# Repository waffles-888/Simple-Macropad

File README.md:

# Simple-Macropad

The Simple Macropad is a 6 key pad with a rotary encoder and an OLED screen. It is also using QMK for its firmware.

# Features:
* 6 Keys
* OLED screen
* Rotary encoder

# CAD Model:
Everything is put together with 4 M3 screws and screws directly into the plastic. The PCB should sit snugly into the space inside the case and has a little bit of plastic extruded from the bottom to keep it flat while being used. It’s printed in two pieces, keeping it simple.

# PCB

This is the PCB which was made inside of KiCAD

# Firmware
My Hackpad uses QMK firmware for it. I want to add VIA support to allow for more customisability.

* 6 keys which will be able to change once theres VIA support
* the rotary encoder allows for volume to be changed
* The OLED screen shows HackPad

# BOM:
* 6x Cherry MX Switches
* 6x 3D printed Keycaps
* 4x M3x16mm screws
* 1x 0.91" 128x32 OLED Display
* 1x EC11 Rotary Encoder
* 1x XIAO RP2040
* 1x Case

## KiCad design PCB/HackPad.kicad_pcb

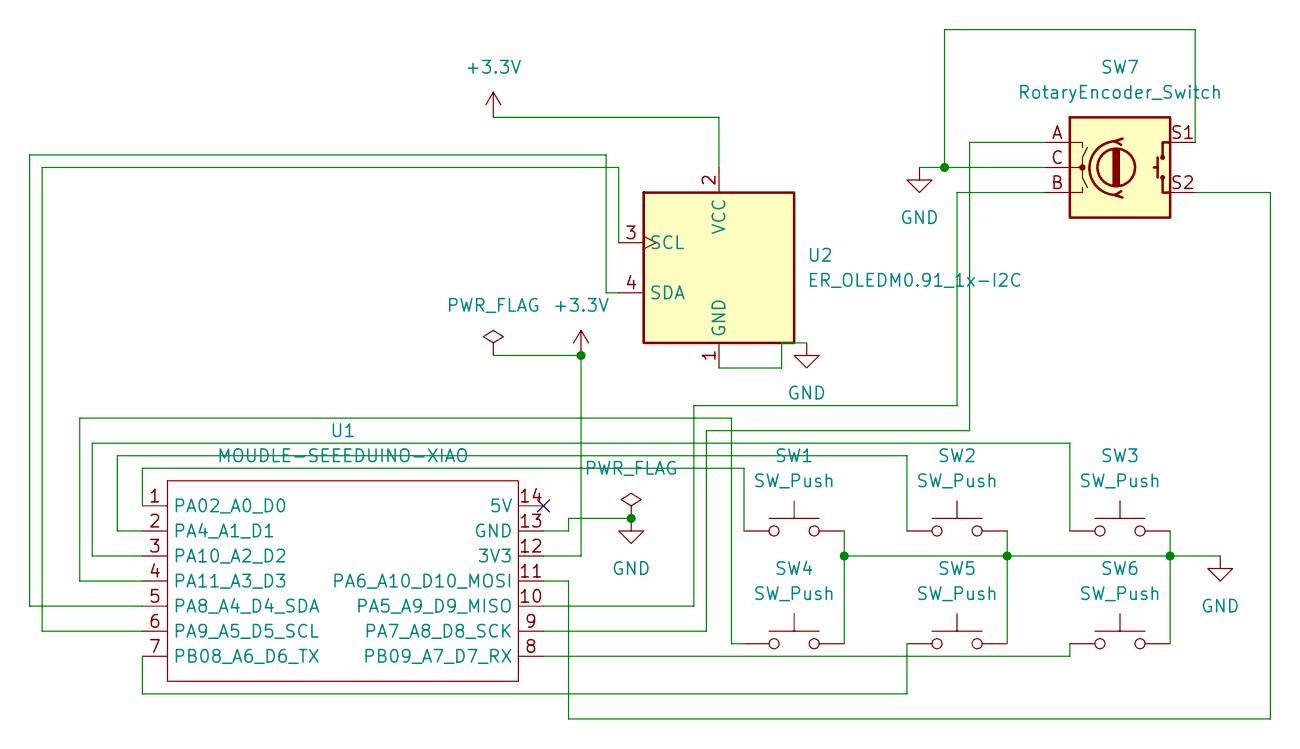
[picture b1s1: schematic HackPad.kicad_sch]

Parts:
SW1, SW2, SW3, SW4, SW5, SW6: SW_Push; SW_Cherry_MX_1.00u_PCB
SW7: RotaryEncoder_Switch; RotaryEncoder_Alps_EC11E-Switch_Vertical_H20mm_CircularMoun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
U1: MOUDLE-SEEEDUINO-XIAO; XIAO-Generic-Hybrid-14P-2.54-21X17.8MM
U2: ER_OLEDM0.91_1x-I2C

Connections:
+3.3V: U1.12 (3V3), U2.2 (VCC)
GND: SW1.2, SW2.2, SW3.2, SW4.2, SW5.2, SW6.2, SW7.C, SW7.S1, U1.13 (GND), U2.1 (GND)
unnamed: SW1.1, U1.1 (PA02_A0_D0)
unnamed: SW2.1, U1.2 (PA4_A1_D1)
unnamed: SW7.B, U1.10 (PA5_A9_D9_MISO)
unnamed: SW7.S2, U1.11 (PA6_A10_D10_MOSI)
unnamed: SW7.A, U1.9 (PA7_A8_D8_SCK)
unnamed: U1.5 (PA8_A4_D4_SDA), U2.4 (SDA)
unnamed: U1.6 (PA9_A5_D5_SCL), U2.3 (SCL)
unnamed: SW3.1, U1.3 (PA10_A2_D2)
unnamed: SW4.1, U1.4 (PA11_A3_D3)
unnamed: SW5.1, U1.7 (PB08_A6_D6_TX)
unnamed: SW6.1, U1.8 (PB09_A7_D7_RX)

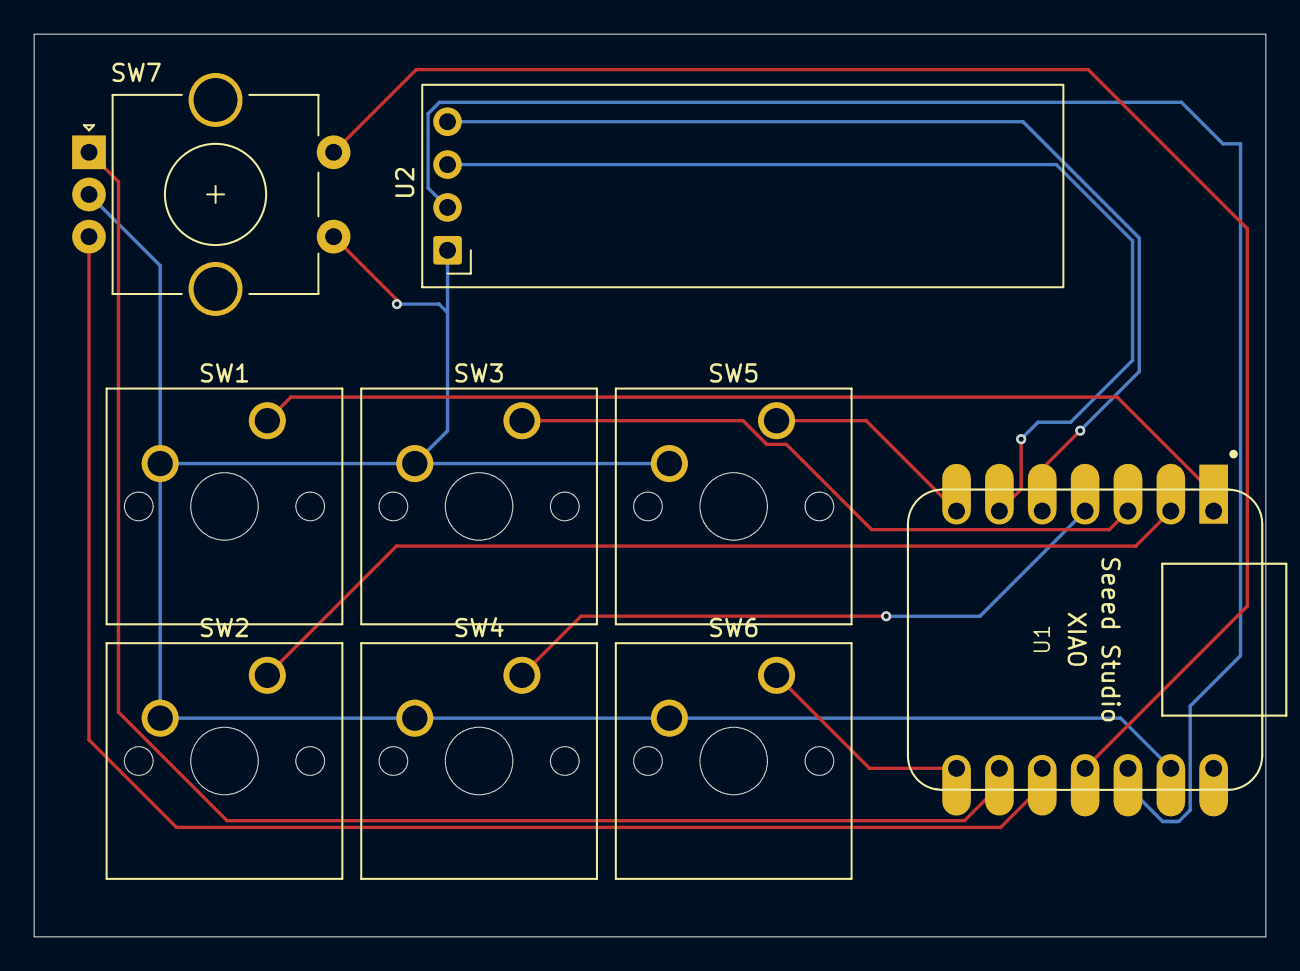
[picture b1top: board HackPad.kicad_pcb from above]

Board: 2 copper layers, 73.0 x 53.5 mm, 9 parts (0 on the bottom side), 13 nets.

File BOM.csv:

"Reference","Qty","Value","DNP","Exclude from BOM","Exclude from Board","Exclude from Simulation","Exclude from Position Files","Footprint","Datasheet"
"SW1,SW2,SW3,SW4,SW5,SW6","6","SW_Push","","","","","${EXCLUDE_FROM_POS_FILES}","Button_Switch_Keyboard:SW_Cherry_MX_1.00u_PCB",""
"SW7","1","RotaryEncoder_Switch","","","","","${EXCLUDE_FROM_POS_FILES}","Rotary_Encoder:RotaryEncoder_Alps_EC11E-Switch_Vertical_H20mm_CircularMountingHoles",""
"U1","1","MOUDLE-SEEEDUINO-XIAO","","","","","${EXCLUDE_FROM_POS_FILES}","footprints:XIAO-Generic-Hybrid-14P-2.54-21X17.8MM",""
"U2","1","ER_OLEDM0.91_1x-I2C","","","","","${EXCLUDE_FROM_POS_FILES}","Display:ER_OLEDM0.91_1x-I2C","https://www.buydisplay.com/download/manual/ER-OLEDM0.91-1_Da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"
